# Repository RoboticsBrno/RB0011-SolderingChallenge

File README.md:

# RB0011 Soldering Challenge

<p align="center">

</p>

Solving the SMD soldering challenge is a great way to learn how to solder SMD components.

<div align="center">
    
</div>

[Soldering Instructions](assembly/index.md){ .md-button .md-button--primary }

The challenge is to solder all the components on the PCB in the shortest time possible.

## Levels
- Level 1 - THT components
- Level 2 - SMD 1206 components
- Level 3 - SMD 0603 components
<!-- - Level 4 - SMD 0402 components (PCB is not complete)
- Level 5 - SMD 0201 components (PCB is not complete) -->

If you manage to plug in all the components correctly, the LED will flash at about 2 Hz when plugged into the USB port.

<div align="center">
    
</div>

!!! info "Attention, L2 has swapped resistor R1 and R2"

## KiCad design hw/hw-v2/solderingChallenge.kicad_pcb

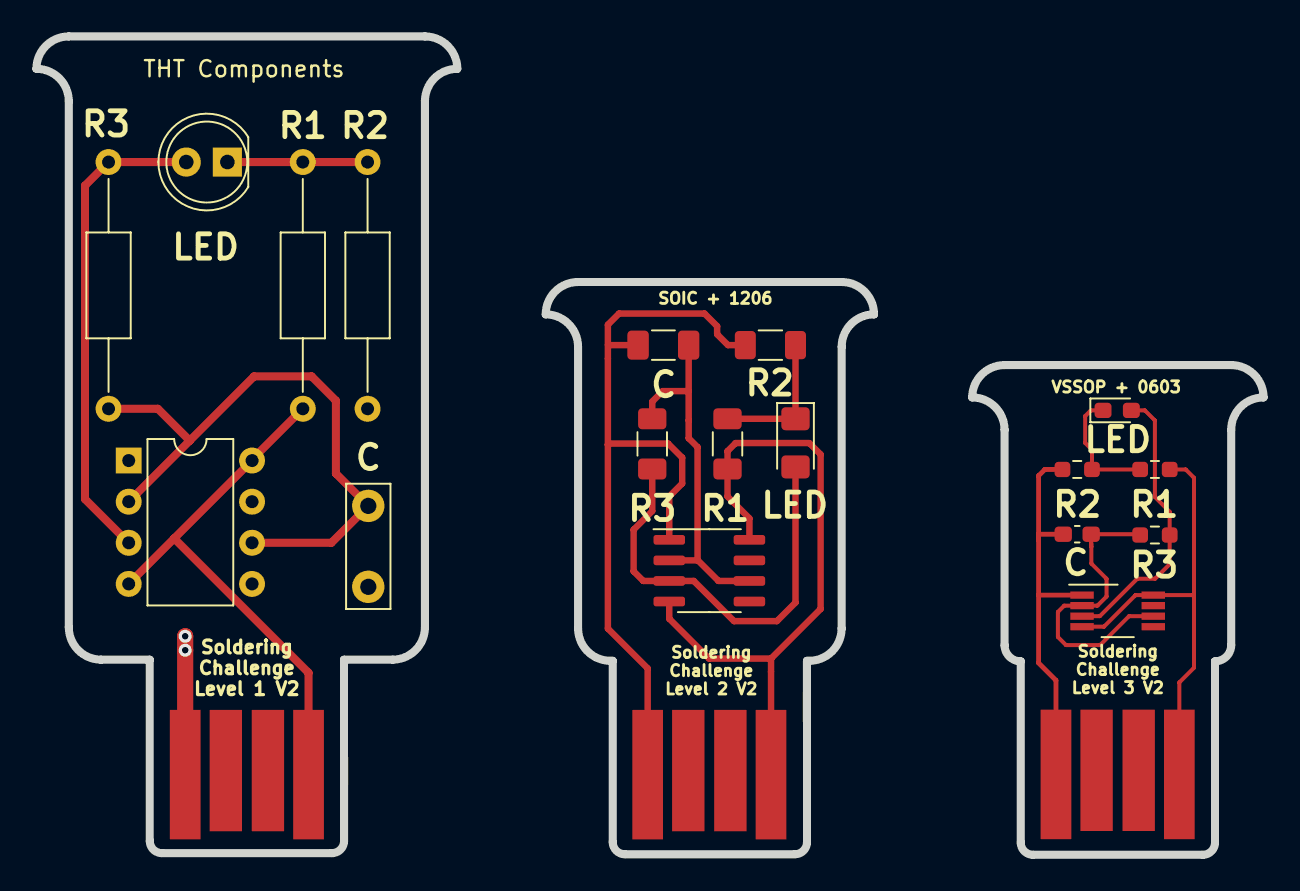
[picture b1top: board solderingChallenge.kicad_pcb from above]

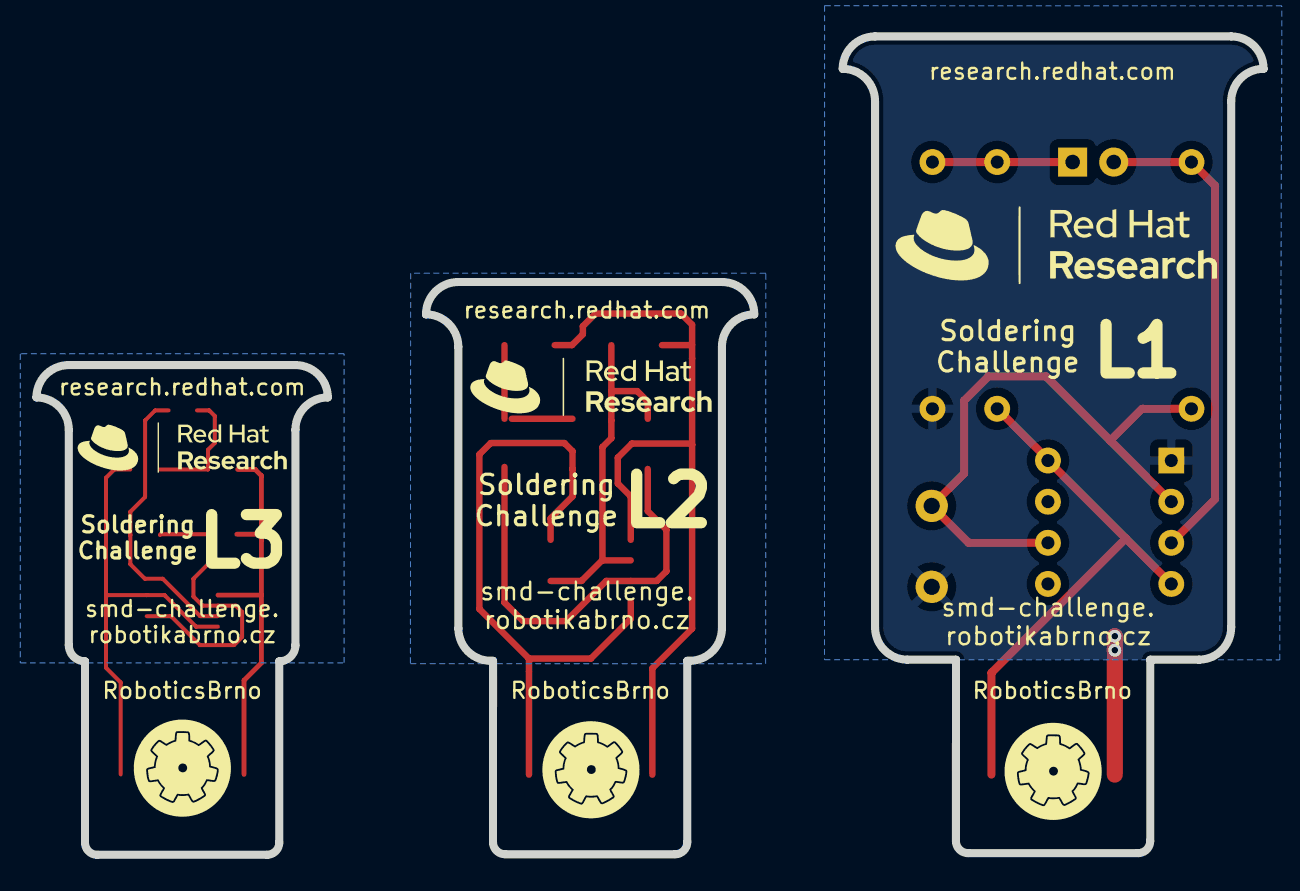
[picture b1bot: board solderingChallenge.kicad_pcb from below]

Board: 2 copper layers, 75.8 x 50.6 mm, 24 parts (3 on the bottom side), 12 nets.

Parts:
C1: 1u; C_Disc_D7.5mm_W2.5mm_P5.00mm
C1#2: 1uF; C_0603_1608Metric_Pad1.08x0.95mm_HandSolder
C2: 1u; C_1206_3216Metric_Pad1.33x1.80mm_HandSolder
D1: LED; LED_D5.0mm
D2: LED; LED_1206_3216Metric_Pad1.42x1.75mm_HandSolder
D3: LED; LED_0603_1608Metric_Pad1.05x0.95mm_HandSolder
J2: USB_A; usb-PCB
Kolecko1, Kolecko1#2, Kolecko1#3: robotarnaLogo; RobotarnaLogo-6mm
R1, R3: 470; R_Axial_DIN0207_L6.3mm_D2.5mm_P15.24mm_Horizontal
R2: 1M; R_0603_1608Metric_Pad0.98x0.95mm_HandSolder
R2#2: 1M; R_Axial_DIN0207_L6.3mm_D2.5mm_P15.24mm_Horizontal
R3#2, R5: 470R; R_1206_3216Metric_Pad1.30x1.75mm_HandSolder
R4: 1M; R_1206_3216Metric_Pad1.30x1.75mm_HandSolder
R5#2, R6: 470; R_0603_1608Metric_Pad0.98x0.95mm_HandSolder
U1: LM555xN; DIP-8_W7.62mm
U2: LMC555xM; SOIC-8_3.9x4.9mm_P1.27mm
U3: LMC555xMM; VSSOP-8_3.0x3.0mm_P0.65mm
U6, U8: USB_A; usb-PCB

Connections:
/Level 1 - THT/GND: C1.2, J2.4 (GND), R3.2, U1.1 (GND)
/Level 1 - THT/VCC: J2.1 (VBUS), R1.1, U1.4 (R), U1.8 (VCC)
/Level 2 - 1206/GND: C2.2, R3#2.1, U2.1 (GND), U6.4 (GND)
/Level 2 - 1206/VCC: R5.2, U2.4 (R), U2.8 (VCC), U6.1 (VBUS)
/Level 3 - 0603/GND: C1#2.2, R6.2, U3.1 (GND), U8.4 (GND)
/Level 3 - 0603/VCC: R5#2.1, U3.4 (R), U3.8 (VCC), U8.1 (VBUS)
unnamed: C1.1, R2#2.1, U1.2 (TR), U1.6 (THR)
unnamed: D1.1 (K), R1.2, R3.1
unnamed: D1.2 (A), R2#2.2, U1.3 (Q)
unnamed: D2.1 (K), R3#2.2, R5.1
unnamed: D2.2 (A), R4.2, U2.3 (Q)
unnamed: D3.1 (K), R5#2.2, R6.1

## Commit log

2023-02-03 Flasher
2023-02-03 .gitignore
2023-02-03 Aesthetics
    - resizing levels 2 and 3
    - centering 555
    - create the same labels for the same parts in all levels
2023-05-12 level 1
2023-05-12 Level 2 and 3
2023-05-19 Add web page
2023-05-20 Add hit counter
2023-05-22 Loga
2023-09-20 Add new guide manual
2023-09-20 Fix plugin - new version
2023-09-20 Remove team
2023-09-23 Documentation Schematics
2023-09-23 Readme clarification
2023-09-26 Fix image, improve texts
2023-10-04 Update assembly, add video plugin, new team info
2023-10-11 Add soldering info, update team
2023-10-17 Fix small issues
2023-10-23 Resistor labels
2023-10-27 Add english version
2023-10-29 Fix wording
2023-10-31 Add transalated images
2023-11-04 Fix .gitignore
2023-11-04 Deployed 6beb212 with MkDocs version: 1.5.3
2024-07-06 Add version 1, update to work with multiple versions
2024-07-06 Deployed c1e99b3 with MkDocs version: 1.5.3
2025-07-02 Updated-Immages
2025-07-02 Update image paths and sizes in soldering instructions
2025-07-07 fix: SDM ch1
2025-07-08 fix: smd V2 L1
2025-07-08 Deployed 1db4da9 with MkDocs version: 1.5.3
